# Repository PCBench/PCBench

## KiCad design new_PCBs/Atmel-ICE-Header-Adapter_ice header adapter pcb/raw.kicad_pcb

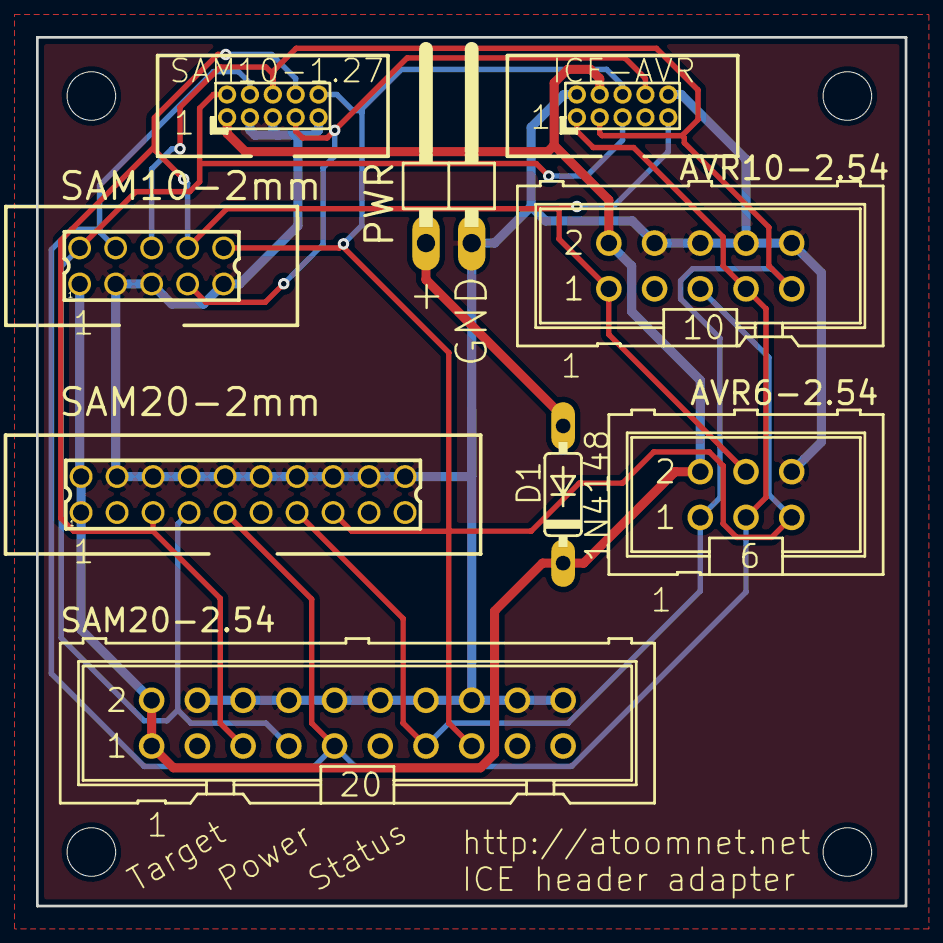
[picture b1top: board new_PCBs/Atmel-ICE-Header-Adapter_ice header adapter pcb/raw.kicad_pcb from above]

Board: 2 copper layers, 48.3 x 48.3 mm, 13 parts (0 on the bottom side), 9 nets.

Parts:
AVR6-2.54: ML6
AVR10-2.54: ML10
D1: 1N4148; DO35-7
ICE-AVR1: PINHEAD_PINHD-2X5; PINHEAD_2X05_127
P1, P2, P3, P4: TST; MountingHole_2.7mm_M2.5
PWR1: PINHD-1X2; 1X02_90
SAM10-1.27: PINHEAD_PINHD-2X5; PINHEAD_2X05_127
SAM10-2: 87758-1016
SAM20-2: 87758-2016
SAM20-2.54: ML20

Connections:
/GND: AVR6-2.54.6, AVR10-2.54.4, AVR10-2.54.6, AVR10-2.54.8, AVR10-2.54.10, ICE-AVR1.2, ICE-AVR1.10, PWR1.2, SAM10-1.27.3, SAM10-1.27.5, SAM10-1.27.9, SAM10-2.3, SAM10-2.5, SAM10-2.9, SAM20-2.4, SAM20-2.6, SAM20-2.8, SAM20-2.10, SAM20-2.12, SAM20-2.14, SAM20-2.16, SAM20-2.18, SAM20-2.20, SAM20-2.54.4, SAM20-2.54.6, SAM20-2.54.8, SAM20-2.54.10, SAM20-2.54.12, SAM20-2.54.14, SAM20-2.54.16, SAM20-2.54.18, SAM20-2.54.20
/NSRST: AVR6-2.54.5, AVR10-2.54.5, ICE-AVR1.6, SAM10-1.27.10, SAM10-2.10, SAM20-2.15, SAM20-2.54.15
/NTRST: ICE-AVR1.8, SAM10-1.27.7, SAM10-2.7
/TCK: AVR6-2.54.3, AVR10-2.54.7, ICE-AVR1.1, SAM10-1.27.4, SAM10-2.4, SAM20-2.9, SAM20-2.54.9
/TDI: AVR6-2.54.4, AVR10-2.54.1, ICE-AVR1.9, SAM10-1.27.8, SAM10-2.8, SAM20-2.5, SAM20-2.54.5
/TDO: AVR6-2.54.1, AVR10-2.54.9, ICE-AVR1.3, SAM10-1.27.6, SAM10-2.6, SAM20-2.13, SAM20-2.54.13
/TMS: ICE-AVR1.5, SAM10-1.27.2, SAM10-2.2, SAM20-2.7, SAM20-2.54.7
/VTG: AVR6-2.54.2, AVR10-2.54.2, D1.C, ICE-AVR1.4, SAM10-1.27.1, SAM10-2.1, SAM20-2.1, SAM20-2.2, SAM20-2.54.1, SAM20-2.54.2
unnamed: D1.A, PWR1.1

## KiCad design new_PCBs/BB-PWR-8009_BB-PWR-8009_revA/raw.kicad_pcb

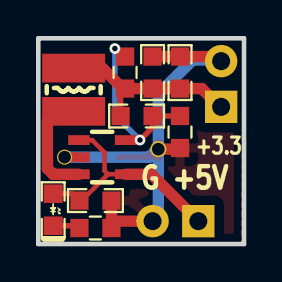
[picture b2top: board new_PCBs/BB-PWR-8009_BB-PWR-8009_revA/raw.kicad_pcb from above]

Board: 2 copper layers, 11.4 x 11.4 mm, 14 parts (0 on the bottom side), 6 nets.

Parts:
C1, C3, C4: 22uF/6.3V; C_0603
C2: 22pF; C_0603
D1: LED_RED_0603; LED_0603_KA
L1: 2.2uH/1.5A/JCR<0.1R/CD32; CD32
P1, P2: HN1x2; HN1x2_Jumper
R1: 4.99K 1%; R_0603_DWS
R2: 1.1K 1%; R_0603_DWS
R3: 2.2K; R_0603_DWS
Ref**: Val**; via_09_07
Ref**#2: Val**; via_09_07
U1: SY8009AAAC(SOT23-5); SOT-23-5

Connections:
GND: C1.2, C3.2, C4.2, P1.2, P2.2, R2.2, R3.1, Ref**.0, Ref**#2.0, U1.2
unnamed: C1.1, D1.2, P1.1, U1.1, U1.4
unnamed: C2.1, C3.1, C4.1, L1.2, P2.1, R1.1
unnamed: C2.2, R1.2, R2.1, U1.5
unnamed: D1.1, R3.2
unnamed: L1.1, U1.3

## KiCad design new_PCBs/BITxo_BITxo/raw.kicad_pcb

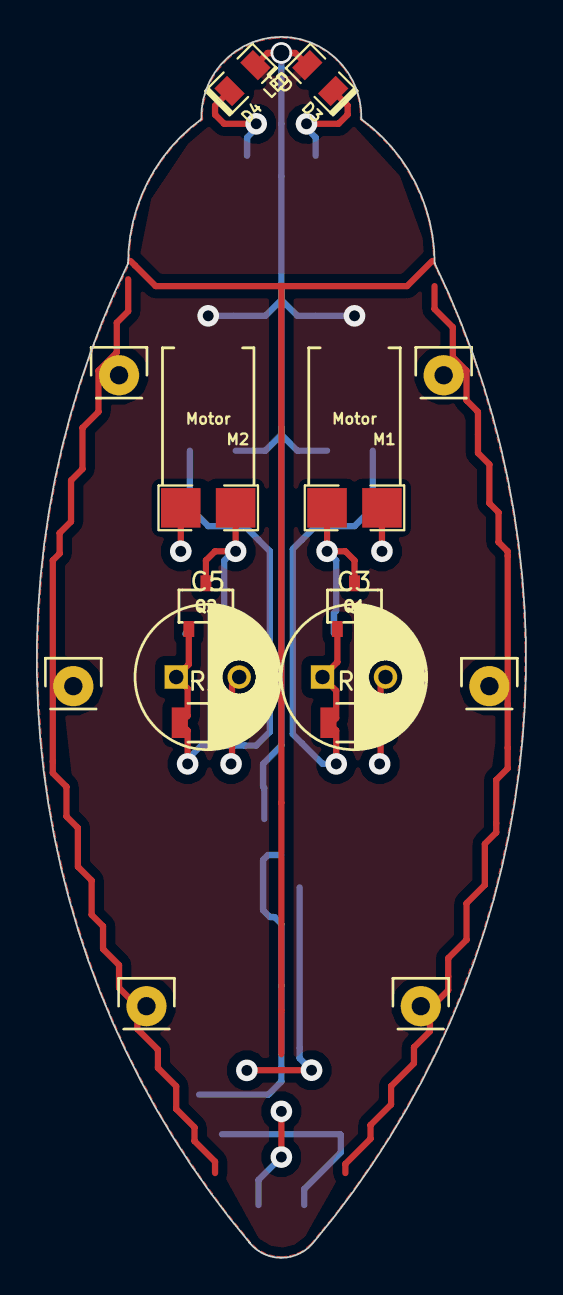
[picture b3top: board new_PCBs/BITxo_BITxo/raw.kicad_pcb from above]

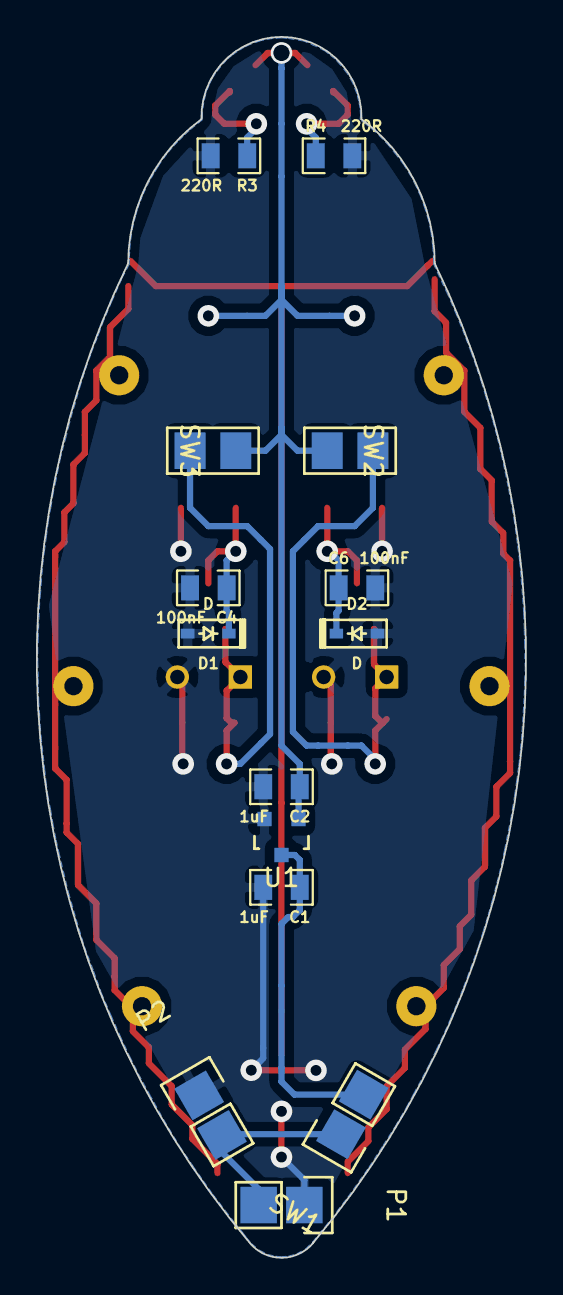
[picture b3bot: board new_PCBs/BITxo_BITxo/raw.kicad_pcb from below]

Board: 2 copper layers, 27.2 x 67.8 mm, 24 parts (14 on the bottom side), 10 nets.

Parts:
C1, C2: 1uF; SMD0805
C3, C5: 1uF; C_Radial_D8_L11.5_P3.5
C4, C6: 100nF; SMD0805
D1, D2: D; SOD-323
D3, D4: LED; SMD0805_LED
M1, M2: Motor; Vibration_motor
P1: Battery Charger; Pads_1x02
P2: Battery; Pads_1x02
Q1, Q2: P-MOSFET; SOT23-5_MOD_PINOUT
R1, R2: 3M3; R_1206
R3, R4: 220R; SMD0805
SW1: ON/OFF; Pads_1x02
SW2, SW3: Endstop; Pads_Endstop
U1: APE8865NL-30-HF-3; SOT-23

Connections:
+3V3: C2.1, D3.2, D4.2, Q1.3, Q2.3, SW2.2, SW3.2, U1.1
+BATT: P1.2, P2.2, SW1.1
GND: C1.2, C2.2, C3.2, C4.2, C5.2, C6.2, D1.2, D2.2, M1.2, M2.1, P1.1, P2.1, R1.2, R2.2, R3.2, R4.2, U1.2
unnamed: C1.1, SW1.2, U1.3
unnamed: C3.1, Q1.2, R1.1, SW2.3
unnamed: C4.1, D1.1, M1.1, Q1.1
unnamed: C5.1, Q2.2, R2.1, SW3.3
unnamed: C6.1, D2.1, M2.2, Q2.1
unnamed: D3.1, R3.1
unnamed: D4.1, R4.1

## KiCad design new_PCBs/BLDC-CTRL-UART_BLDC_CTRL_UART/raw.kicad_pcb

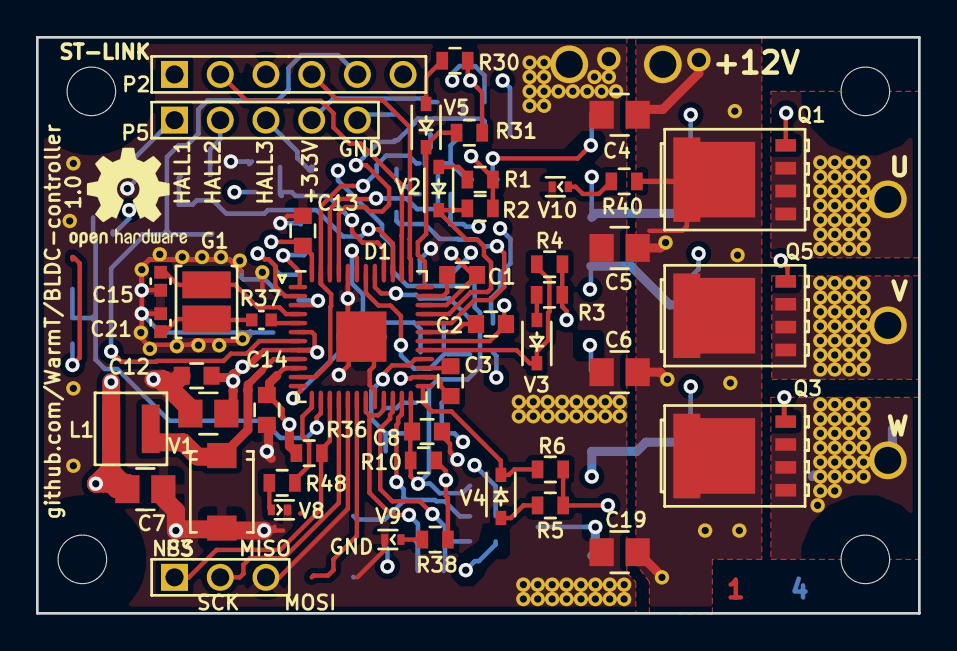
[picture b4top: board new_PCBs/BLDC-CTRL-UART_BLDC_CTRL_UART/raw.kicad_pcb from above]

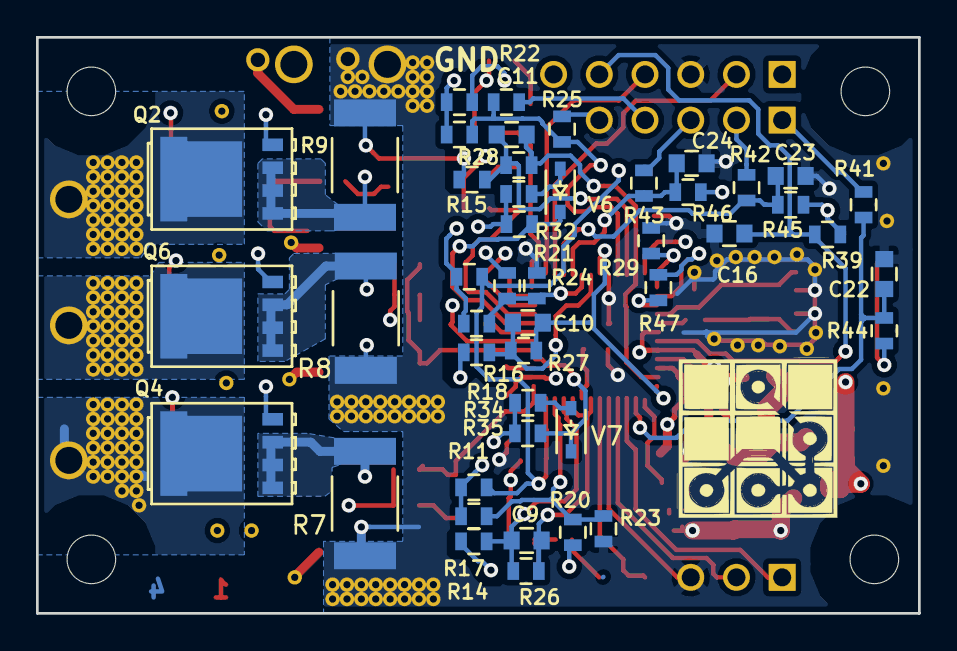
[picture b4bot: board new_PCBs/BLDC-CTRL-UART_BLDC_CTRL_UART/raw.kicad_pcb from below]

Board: 4 copper layers, 49.0 x 32.0 mm, 92 parts (46 on the bottom side), 61 nets.

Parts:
C1, C2, C3, C12, C13, C14: 100n; C_0603
C4, C5, C6, C17, C19: 220n; C_0805
C7: 47u; C_0805
C8: 1n0; C_0603
C9, C10, C11: 100p; C_0603
C15, C21: 10p; C_0402
C16: 3n3; C_0603
C22, C23, C24: 10p; C_0603
D1: STSPIN32F0; QFN-48-1EP_7x7mm_Pitch0.5mm
G1: NX3225GD; Crystal_3225
L1: SRN3015-220M; BOURNS-SRN3015
P2: CONN_01X06; PINHEAD1-6
P3: CONN_01X03; PINHEAD1-3
P5: CONN_01X05; PINHEAD1-5
Q1, Q2, Q3, Q4, Q5, Q6: PSMN2R0-30YLD; SOT-669_LFPAK56
R1, R3, R5, R30, R32, R34, R47: 10R; R_0603
R2, R4, R6, R31, R33, R35: 62R; R_0603
R7, R8, R9: 0R01; R_2512
R10: 46k4; R_0603
R11, R12, R13, R29, R36, R40: 2k2; R_0603
R14, R15, R16, R41, R42, R43: 1k0; R_0603
R17, R18, R19, R23, R24, R25, R48: 560R; R_0603
R20, R21, R22: 8k2; R_0603
R26, R27, R28: 15k; R_0603
R37: 10R; R_0402_MOST
R38: 330R; R_0603
R39: 39k; R_0603
R44, R45, R46: 10k; R_0603
V1: STPS1L60A; SMA
V2, V3, V4, V5, V6, V7: 4148WS; SOD-323
V8, V9, V10: LED_ALT; LED_0402

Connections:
+3V3: C7.1, C13.1, C14.1, D1.10, D1.48, L1.1, P2.1, P5.4, R10.2, R20.1, R21.1, R22.1, R36.1, R38.1, R39.1, R44.1, R45.1, R46.1
+12V: C4.1, C5.1, C6.1, C12.1, C17.1, C19.1, D1.6, D1.8, Q1.5, Q3.5, Q5.5, R40.1
/HALL1/A+: C22.1, D1.11, R41.1, R44.2
/HALL2/B+: C23.1, D1.12, R42.1, R45.2
/HALL3/Z+: C24.1, D1.13, R43.1, R46.2
/HSU: Q1.4, R1.1, R2.1
/HSV: Q5.4, R3.1, R4.1
/HSW: Q3.4, R5.1, R6.1
/LSU: Q2.4, R30.1, R31.1
/LSV: Q6.4, R32.1, R33.1
/LSW: Q4.4, R34.1, R35.1
/NRST: C16.1, D1.7, P2.5, R39.2
/OC_COMP: C8.1, D1.24, R10.1, R11.2, R12.2, R13.2
/OP1N: C9.2, D1.22, R14.2, R26.2
/OP1P: D1.23, R17.1, R20.2, R23.1
/OP2N: C10.2, D1.42, R16.2, R27.2
/OP2P: D1.41, R18.1, R21.2, R24.1
/OP3N: C11.2, D1.46, R15.2, R28.2
/OP3P: D1.45, R19.1, R22.2, R25.1
/OP4N: D1.2, R47.2
/OP4P: D1.1, R29.1
/OSC_IN: C15.1, D1.4, G1.1
/OUTU: C1.1, D1.34, Q1.1, Q1.2, Q1.3, Q2.5
/OUTV: C2.1, D1.30, Q5.1, Q5.2, Q5.3, Q6.5
/OUTW: C3.1, D1.26, Q3.1, Q3.2, Q3.3, Q4.5
/PA2_LED: R48.2, V8.2
/SW: D1.9, L1.2, V1.1
/SWCLK: D1.38, P2.2
/SWDIO: D1.37, P2.4
/U_ADC: C11.1, D1.16, D1.47, R28.1
/VBOOSTU: C1.2, D1.35
/VBOOSTV: C2.2, D1.31
/VBOOSTW: C3.2, D1.27
/V_ADC: C10.1, D1.15, D1.43, R27.1
/W_ADC: C9.1, D1.14, D1.21, R26.1
GND: C4.2, C5.2, C6.2, C7.2, C8.2, C12.2, C13.2, C14.2, C15.2, C16.2, C17.2, C19.2, C21.2, C22.2, C23.2, C24.2, D1.20, D1.44, D1.49, P2.3, P3.3, P5.5, R7.2, R8.2, R9.2, R14.1, R15.1, R16.1, R23.2, R24.2, R25.2, R29.2, V1.2, V8.1, V9.1, V10.1
unnamed: C21.1, G1.2, R37.2
unnamed: D1.3, R47.1
unnamed: D1.5, R37.1
unnamed: D1.25, R6.2, V4.1
unnamed: D1.28, R35.2, V7.1
unnamed: D1.29, R4.2, V3.1
unnamed: D1.32, R33.2, V6.1
unnamed: D1.33, R2.2, V2.1
unnamed: D1.36, R31.2, V5.1
unnamed: D1.39, P3.1
unnamed: D1.40, P3.2
unnamed: P5.1, R41.2
unnamed: P5.2, R42.2
unnamed: P5.3, R43.2
unnamed: R1.2, V2.2
unnamed: R3.2, V3.2
unnamed: R5.2, V4.2
unnamed: R30.2, V5.2
unnamed: R32.2, V6.2
unnamed: R34.2, V7.2
unnamed: R38.2, V9.2
unnamed: R40.2, V10.2
U_SENSE_P: Q2.1, Q2.2, Q2.3, R9.1, R13.1, R19.2
V_SENSE_P: Q6.1, Q6.2, Q6.3, R8.1, R12.1, R18.2
W_SENSE_P: Q4.1, Q4.2, Q4.3, R7.1, R11.1, R17.2

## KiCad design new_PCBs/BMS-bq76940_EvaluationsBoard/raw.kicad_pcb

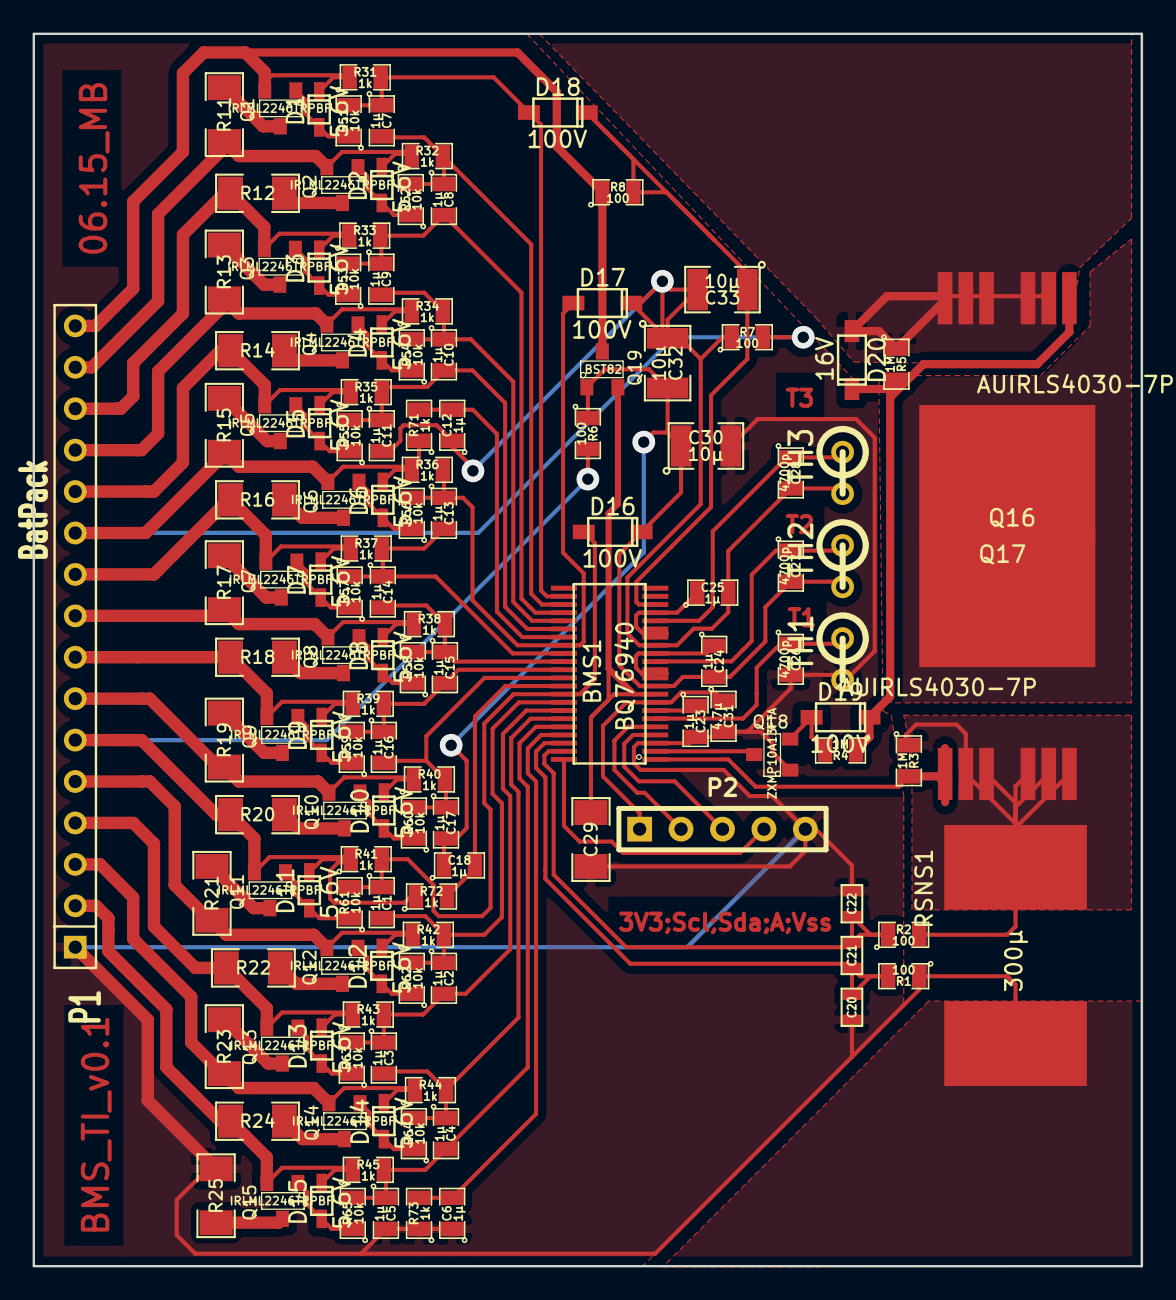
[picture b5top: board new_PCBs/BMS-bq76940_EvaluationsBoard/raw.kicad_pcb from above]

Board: 2 copper layers, 67.9 x 75.6 mm, 134 parts (0 on the bottom side), 87 nets.

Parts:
BMS1: BQ76940
C1, C2, C3, C4, C5, C6, C7, C8, C9, C10, C11, C12, C13, C14, C15, C16, C17, C18, C23, C24, C25: 1µ; SM0805
C20, C21, C22: 0.1µ; SM0603
C26, C27, C28: 4700p; SM0805
C29: 1µ; SM1206
C30, C32, C33: 10µ; SM1210
C31: 4.7µ; SM0805
D1, D2, D3, D4, D5, D6, D7, D8, D9, D10, D11, D12, D13, D14, D15: 5.6V; SOD323
D16, D17, D18, D19: 100V; SOD123
D20: 16V; SOD123
P1: BatPack; SIL-16
P2: µC; PIN_ARRAY_5x1
Q1, Q2, Q3, Q4, Q5, Q6, Q7, Q8, Q9, Q10, Q11, Q12, Q13, Q14, Q15: IRLML2246TRPBF; SOT23
Q16, Q17: AUIRLS4030-7P
Q18: ZXMP10A13FTA; SOT23
Q19: BST82; SOT23
R1, R2, R6, R7, R8: 100; SM0805
R3, R4, R5: 1M; SM0805
R11, R12, R13, R14, R15, R16, R17, R18, R19, R20, R21, R22, R23, R24, R25: 39; SM1206
R31, R32, R33, R34, R35, R36, R37, R38, R39, R40, R41, R42, R43, R44, R45, R71, R72, R73: 1k; SM0805
R51, R52, R53, R54, R55, R56, R57, R58, R59, R60, R61, R62, R63, R64, R65: 10k; SM0805
RSNS1: 300µ; WSLP5931
TH1, TH2, TH3: THERMISTOR; R1

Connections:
/BatPack/C1: D15.2, P1.2, Q15.2, R24.1, R45.1
/BatPack/C2: D14.2, P1.3, Q14.2, R23.1, R44.1
/BatPack/C3: D13.2, P1.4, Q13.2, R22.1, R43.1
/BatPack/C4: D12.2, P1.5, Q12.2, R21.1, R42.1
/BatPack/C6: D10.2, P1.7, Q10.2, R19.1, R40.1
/BatPack/C7: D9.2, P1.8, Q9.2, R18.1, R39.1
/BatPack/C8: D8.2, P1.9, Q8.2, R17.1, R38.1
/BatPack/C9: D7.2, P1.10, Q7.2, R16.1, R37.1
/BatPack/C11: D5.2, P1.12, Q5.2, R14.1, R35.1
/BatPack/C12: D4.2, P1.13, Q4.2, R13.1, R34.1
/BatPack/C13: D3.2, P1.14, Q3.2, R12.1, R33.1
/BatPack/C14: D2.2, P1.15, Q2.2, R11.1, R32.1
/BatPack/VC0: BMS1.41, C6.2, R73.2
/BatPack/VC1: BMS1.40, C4.2, C5.1, R45.2, R65.2
/BatPack/VC2: BMS1.39, C3.2, C4.1, R44.2, R64.2
/BatPack/VC3: BMS1.38, C2.2, C3.1, R43.2, R63.2
/BatPack/VC4: BMS1.37, C1.2, C2.1, R42.2, R62.2
/BatPack/VC5: BMS1.36, C1.1, D16.1, R41.2, R61.2
/BatPack/VC6: BMS1.34, C16.2, C17.1, R40.2, R60.2
/BatPack/VC7: BMS1.33, C15.2, C16.1, R39.2, R59.2
/BatPack/VC8: BMS1.32, C14.2, C15.1, R38.2, R58.2
/BatPack/VC9: BMS1.31, C13.2, C14.1, R37.2, R57.2
/BatPack/VC10: BMS1.30, C13.1, D17.1, R36.2, R56.2
/BatPack/VC11: BMS1.28, C10.2, C11.1, R35.2, R55.2
/BatPack/VC12: BMS1.27, C9.2, C10.1, R34.2, R54.2
/BatPack/VC13: BMS1.26, C8.2, C9.1, R33.2, R53.2
/BatPack/VC14: BMS1.25, C7.2, C8.1, R32.2, R52.2
/BatPack/VC15: BMS1.24, C7.1, D18.1, R31.2, R51.2
/COM/BAT: BMS1.20, C33.1, D18.2, R8.2
/COM/CHG: BMS1.2, Q18.3
/COM/DSC: BMS1.1, Q16.1, R3.2
/COM/REGOUT: BMS1.8, C31.1, P2.1
/COM/REGSRC: BMS1.9, C29.1, Q19.2
/COM/SCL: BMS1.5, P2.2
/COM/SDA: BMS1.4, P2.3
/COM/SRN: BMS1.43, C21.2, C22.1, R2.1
/COM/SRP: BMS1.42, C20.2, C21.1, R1.2
A: D11.2, P1.6, Q11.2, R6.2, R20.1, R41.1, R72.1
ALERT: BMS1.44, P2.4
B: D6.2, P1.11, Q6.2, R7.2, R15.1, R36.1, R71.1
unnamed: D5.1, Q5.1, R55.1
unnamed: D3.1, Q3.1, R53.1
unnamed: D4.1, Q4.1, R54.1
unnamed: D6.1, Q6.1, R56.1
unnamed: D2.1, Q2.1, R52.1
unnamed: D1.1, Q1.1, R51.1
unnamed: Q3.3, R13.2
unnamed: Q4.3, R14.2
unnamed: Q5.3, R15.2
unnamed: Q6.3, R16.2
unnamed: Q7.3, R17.2
unnamed: Q8.3, R18.2
unnamed: D9.1, Q9.1, R59.1
unnamed: Q9.3, R19.2
unnamed: D10.1, Q10.1, R60.1
unnamed: Q1.3, R11.2
unnamed: Q2.3, R12.2
unnamed: Q14.3, R24.2
unnamed: Q13.3, R23.2
unnamed: Q12.3, R22.2
unnamed: Q11.3, R21.2
unnamed: Q10.3, R20.2
unnamed: Q15.3, R25.2
unnamed: D11.1, Q11.1, R61.1
unnamed: D12.1, Q12.1, R62.1
unnamed: D14.1, Q14.1, R64.1
unnamed: D7.1, Q7.1, R57.1
unnamed: D8.1, Q8.1, R58.1
unnamed: D13.1, Q13.1, R63.1
unnamed: D15.1, Q15.1, R65.1
unnamed: BMS1.7, C23.1
unnamed: BMS1.16, BMS1.17, BMS1.19, C25.1
unnamed: BMS1.11, BMS1.12, BMS1.14, C24.1
unnamed: D19.2, D20.2, Q17.1, R4.1, R5.2
unnamed: Q16.8, Q17.8
unnamed: D19.1, Q18.2, R4.2
unnamed: Q16.2, Q16.3, Q16.5, Q16.6, Q16.7, R2.2, R3.1, RSNS1.1
PACK+: D1.2, P1.16, Q1.2, Q19.3, R8.1, R31.1
PACK-: D20.1, Q17.2, Q17.3, Q17.5, Q17.6, Q17.7, R5.1
TS1: BMS1.6, C26.1, TH1.1
TS2: BMS1.13, C27.1, TH2.1
TS3: BMS1.18, C28.1, TH3.1
VC5B: BMS1.35, C18.2, R72.2
VC5x: BMS1.10, C17.2, C18.1, C24.2, C27.2, C30.1, C32.2, D16.2, Q19.1, R6.1, TH2.2
VC10B: BMS1.29, C12.2, R71.2
VC10x: BMS1.15, C11.2, C12.1, C25.2, C28.2, C32.1, C33.2, D17.2, R7.1, TH3.2
VSS: BMS1.3, C5.2, C6.1, C20.1, C22.2, C23.2, C26.2, C29.2, C30.2, C31.2, P1.1, P2.5, Q18.1, R1.1, R25.1, R73.1, RSNS1.2, TH1.2
